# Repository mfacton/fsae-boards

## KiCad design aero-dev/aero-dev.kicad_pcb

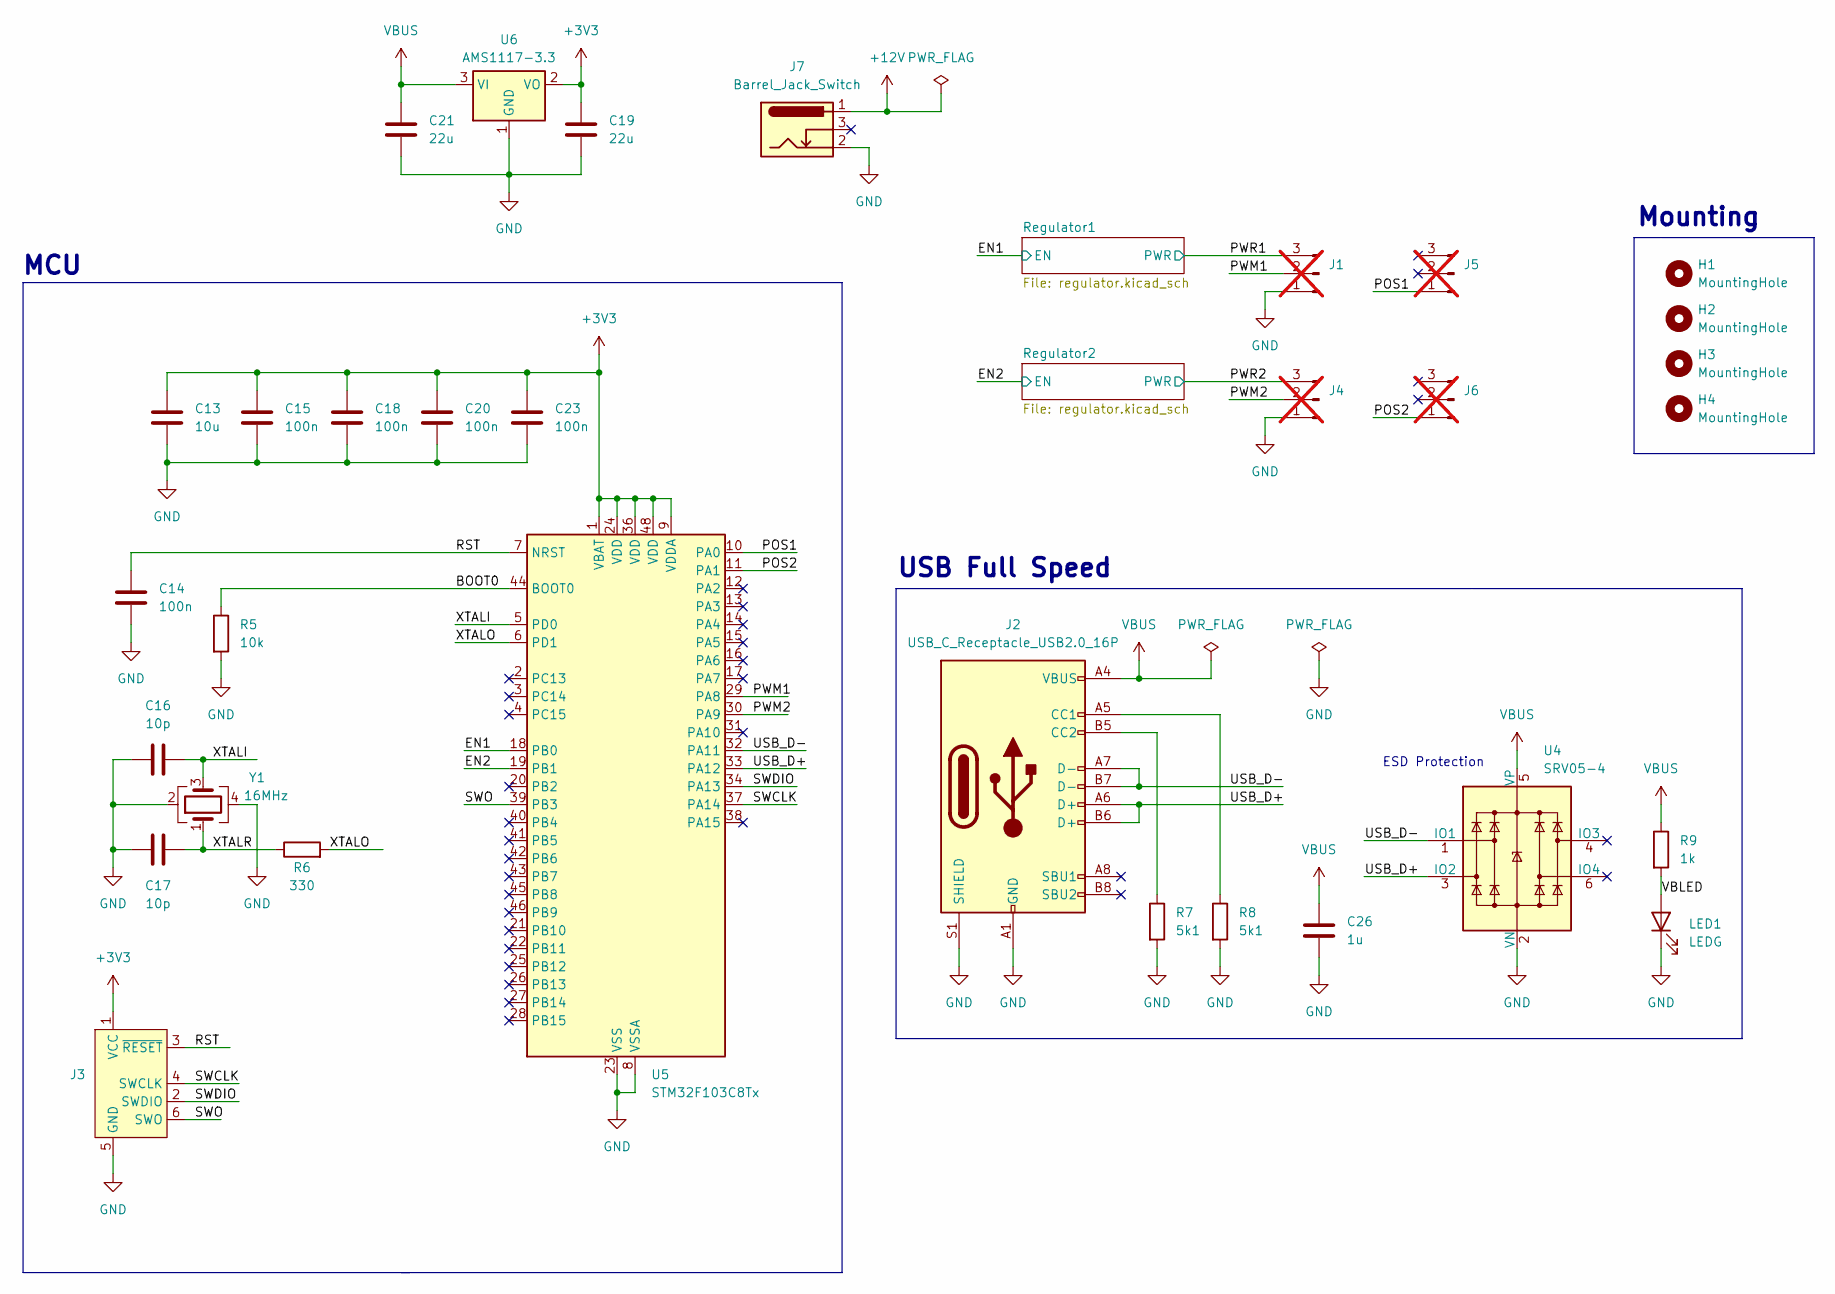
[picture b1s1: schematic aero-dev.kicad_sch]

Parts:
C13: 10u; C_0603_1608Metric
C14, C15, C18, C20, C23: 100n; C_0402_1005Metric
C16, C17: 10p; C_0402_1005Metric
C19: 22u; C_0603_1608Metric
C21: 22u; C_0805_2012Metric
C26: 1u; C_0402_1005Metric
H1, H2, H3, H4: MountingHole; MountingHole_3.2mm_M3
J1, J4, J5, J6: Conn_01x03_Pin; PinHeader_1x03_P2.54mm_Vertical; not fitted
J2: USB_C_Receptacle_USB2.0_16P; USB_C_Receptacle_GCT_USB4105-xx-A_16P_TopMnt_Horizontal; LCSC C165948
J3: Conn_ARM_SWD_TagConnect_TC2030-NL; Tag-Connect_TC2030-IDC-NL_2x03_P1.27mm_Vertical
J7: Barrel_Jack_Switch; BarrelJack_Horizontal; LCSC C319099
LED1: LEDG; LED_0603_1608Metric; LCSC C2986059
R5: 10k; R_0402_1005Metric
R6: 330; R_0402_1005Metric
R7, R8: 5k1; R_0402_1005Metric
R9: 1k; R_0402_1005Metric
U4: SRV05-4; SOT-23-6; LCSC C7420376
U5: STM32F103C8Tx; LQFP-48_7x7mm_P0.5mm
U6: AMS1117-3.3; SOT-223-3_TabPin2
Y1: 16MHz; Crystal_SMD_3225-4Pin_3.2x2.5mm

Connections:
+3V3: C13.1, C15.1, C18.1, C19.1, C20.1, C23.1, J3.1 (VCC), U5.1 (VBAT), U5.9 (VDDA), U5.24 (VDD), U5.36 (VDD), U5.48 (VDD), U6.2 (VO)
+12V: J7.1; also elsewhere on the board
/BOOT0: R5.1, U5.44 (BOOT0)
/EN1: U5.18 (PB0); also elsewhere on the board
/EN2: U5.19 (PB1); also elsewhere on the board
/POS1: J5.1, U5.10 (PA0)
/POS2: J6.1, U5.11 (PA1)
/PWM1: J1.2, U5.29 (PA8)
/PWM2: J4.2, U5.30 (PA9)
/PWR1: J1.3; also elsewhere on the board
/PWR2: J4.3; also elsewhere on the board
/RST: C14.1, J3.3 (~RESET), U5.7 (NRST)
/SWCLK: J3.4 (SWCLK), U5.37 (PA14)
/SWDIO: J3.2 (SWDIO), U5.34 (PA13)
/SWO: J3.6 (SWO), U5.39 (PB3)
/USB_D+: J2.A6 (D+), J2.B6 (D+), U4.3 (IO2), U5.33 (PA12)
/USB_D-: J2.A7 (D-), J2.B7 (D-), U4.1 (IO1), U5.32 (PA11)
/VBLED: LED1.2 (A), R9.2
/XTALI: C16.2, U5.5 (PD0), Y1.3
/XTALO: R6.2, U5.6 (PD1)
/XTALR: C17.2, R6.1, Y1.1
GND: C13.2, C14.2, C15.2, C16.1, C17.1, C18.2, C19.2, C20.2, C21.2, C23.2, C26.2, J1.1, J2.A1 (GND), J2.A12 (GND), J2.B1 (GND), J2.B12 (GND), J2.S1 (SHIELD), J3.5 (GND), J4.1, J7.2, LED1.1 (K), R5.2, R7.2, R8.2, U4.2 (VN), U5.8 (VSSA), U5.23 (VSS), U5.35 (VSS), U5.47 (VSS), U6.1 (GND), Y1.2, Y1.4; also elsewhere on the board
unnamed: J2.A5 (CC1), R8.1
unnamed: J2.B5 (CC2), R7.1
VBUS: C21.1, C26.1, J2.A4 (VBUS), J2.A9 (VBUS), J2.B4 (VBUS), J2.B9 (VBUS), R9.1, U4.5 (VP), U6.3 (VI)

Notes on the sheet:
Mounting
ESD Protection
MCU
USB Full Speed

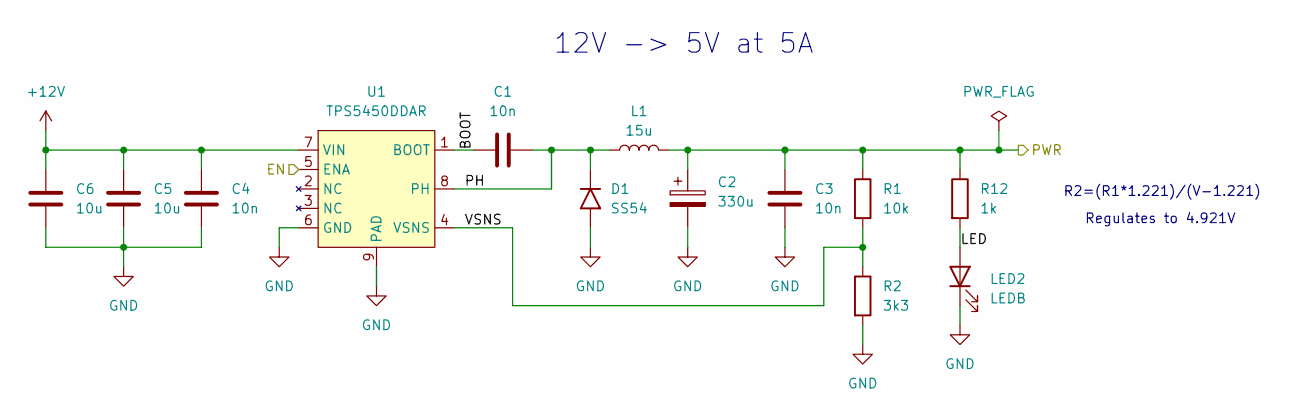
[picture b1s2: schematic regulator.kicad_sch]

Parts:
C1, C3, C4: 10n; C_0402_1005Metric
C2: 330u; CP_Elec_10x10.5; LCSC C280411
C5, C6: 10u; C_1206_3216Metric; LCSC C13585
D1: SS54; D_SMA
L1: 15u; L_12x12mm_H4.5mm; LCSC C149596
LED2: LEDB; LED_0603_1608Metric
R1: 10k; R_0603_1608Metric_Pad0.98x0.95mm_HandSolder
R2: 3k3; R_0603_1608Metric_Pad0.98x0.95mm_HandSolder
R12: 1k; R_0402_1005Metric
U1: TPS5450DDAR; Texas_R-PDSO-G8_EP2.95x4.9mm_Mask2.4x3.1mm

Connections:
+12V: C4.1, C5.1, C6.1, U1.7 (VIN); also elsewhere on the board
/EN1: U1.5 (ENA); also elsewhere on the board
/PWR1: C2.1, C3.1, L1.2, R1.1, R12.1; also elsewhere on the board
/Regulator1/BOOT: C1.2, U1.1 (BOOT)
/Regulator1/LED: LED2.2 (A), R12.2
/Regulator1/PH: C1.1, D1.1 (K), L1.1, U1.8 (PH)
/Regulator1/VSNS: R1.2, R2.1, U1.4 (VSNS)
GND: C2.2, C3.2, C4.2, C5.2, C6.2, D1.2 (A), LED2.1 (K), R2.2, U1.6 (GND), U1.9 (PAD); also elsewhere on the board

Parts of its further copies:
C7, C8: 10u; C_1206_3216Metric; LCSC C13585
C9, C10, C12: 10n; C_0402_1005Metric
C11: 330u; CP_Elec_10x10.5; LCSC C280411
D2: SS54; D_SMA
L2: 15u; L_12x12mm_H4.5mm; LCSC C149596
LED3: LEDB; LED_0603_1608Metric
R3: 10k; R_0603_1608Metric_Pad0.98x0.95mm_HandSolder
R4: 3k3; R_0603_1608Metric_Pad0.98x0.95mm_HandSolder
R13: 1k; R_0402_1005Metric
U2: TPS5450DDAR; Texas_R-PDSO-G8_EP2.95x4.9mm_Mask2.4x3.1mm

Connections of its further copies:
+12V: C7.1, C8.1, C9.1, U2.7 (VIN); also elsewhere on the board
/EN2: U2.5 (ENA); also elsewhere on the board
/PWR2: C11.1, C12.1, L2.2, R3.1, R13.1; also elsewhere on the board
/Regulator2/BOOT: C10.2, U2.1 (BOOT)
/Regulator2/LED: LED3.2 (A), R13.2
/Regulator2/PH: C10.1, D2.1 (K), L2.1, U2.8 (PH)
/Regulator2/VSNS: R3.2, R4.1, U2.4 (VSNS)
GND: C7.2, C8.2, C9.2, C11.2, C12.2, D2.2 (A), LED3.1 (K), R4.2, U2.6 (GND), U2.9 (PAD); also elsewhere on the board

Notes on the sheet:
R2=(R1*1.221)/(V-1.221)
Regulates to 4.921V
12V -> 5V at 5A

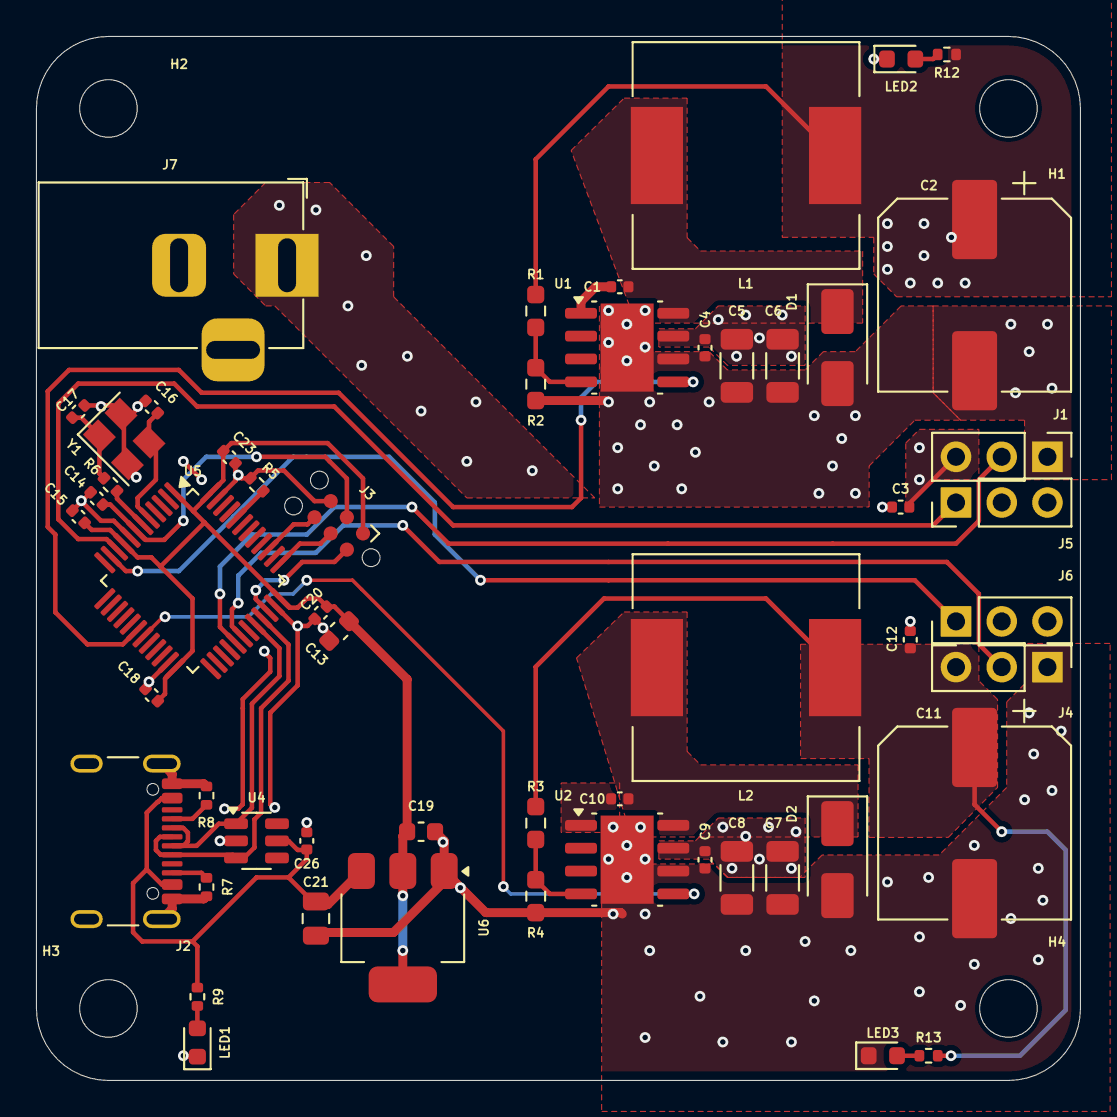
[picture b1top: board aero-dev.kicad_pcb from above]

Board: 2 copper layers, 58.0 x 58.0 mm, 58 parts (0 on the bottom side), 33 nets.

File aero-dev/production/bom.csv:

Designator,Footprint,Quantity,Value,LCSC Part #
"C1, C10, C12, C3, C4, C9",0402,6,10n,
"C11, C2",CP_Elec_10x10.5,2,330u,C280411
C13,0603,1,10u,
"C14, C15, C18, C20, C23",0402,5,100n,
"C16, C17",0402,2,10p,
"C19, C21",0603,2,22u,
C26,0402,1,1u,
"C5, C6, C7, C8",1206,4,10u,C13585
"D1, D2",D_SMA,2,SS54,
"J1, J4, J5, J6",PinHeader_1x03_P2.54mm_Vertical,4,Conn_01x03_Pin,
J2,USB_C_Receptacle_GCT_USB4105-xx-A_16P_TopMnt_Horizontal,1,USB_C_Receptacle_USB2.0_16P,C165948
J7,BarrelJack_Horizontal,1,Barrel_Jack_Switch,C319099
"L1, L2",L_12x12mm_H4.5mm,2,15u,C149596
LED1,0603,1,LEDG,
"LED2, LED3",0603,2,LEDB,
"R1, R3",0603,2,10k,
"R12, R13, R9",0402,3,1k,
"R2, R4",0603,2,3k3,
R5,0402,1,10k,
R6,0402,1,330,
"R7, R8",0402,2,5k1,
"U1, U2",Texas_R-PDSO-G8_EP2.95x4.9mm_Mask2.4x3.1mm,2,TPS5450DDAR,
U4,SOT-23-6,1,SRV05-4,C7420376
U5,LQFP-48_7x7mm_P0.5mm,1,STM32F103C8Tx,
U6,SOT-223-3_TabPin2,1,AMS1117-3.3,
Y1,Crystal_SMD_3225-4Pin_3.2x2.5mm,1,16MHz,

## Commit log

2024-05-10 Add gitignore
2024-05-12 Testing git
2024-05-12 Remove testing file
2024-05-14 Add kigit manager file
2024-05-14 Add status file
2024-05-15 Add branch bms-carrier
2024-05-15 Checkout bms-carrier by Miguel Flores-Acton
2024-05-19 Add branch aero-dev
2024-05-19 Checkout aero-dev by Miguel Flores-Acton
2024-05-19 Remove kicad ignores to fix later
2024-05-19 Update .gitignore for lck and backups
2024-05-19 Update .gitignore for kicad files
2024-05-19 Finish schematic, positions and zones
2024-05-19 Fix .log and .lck files
2024-05-20 Ignore backups of production files
2024-05-20 Make initial production file
2024-05-20 Finalize production files and minor edits
